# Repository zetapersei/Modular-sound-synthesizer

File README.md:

# Analog Modular Synthesizer

An analog modular synthesizer project inspired by the architecture of classic
synthesizers, including those in the Moog tradition. It grew out of a personal
project I worked on between 1978 and 1980; the schematics preserve that idea
and have since been collected and redrawn in KiCad.

The repository contains the project's electronic design documentation: a
hierarchical top-level schematic, individual module schematics, a PCB project,
and a netlist.

## Modules

| Module | Function |
| --- | --- |
| **VCO** | Voltage-controlled oscillator: generates the basic signal. |
| **VCF** | Voltage-controlled filter, identified in the schematic as the PAiA 4730 filter. |
| **VCA** | Voltage-controlled amplifier: controls the signal level. |
| **ADSR** | Envelope generator for shaping the sound over time. |
| **LFO** | Low-frequency oscillator for slow modulation. |
| **Noise generator** | Noise source for additional timbres and modulation. |
| **Audio mixer** | Combines audio sources. |
| **Keyboard encoder** | Schematic for a 49-key musical keyboard interface. |

The modules are organized in the main schematic
[`analog_synth.kicad_sch`](analog_synth.kicad_sch); each circuit also has its
own separate schematic. Module filenames correspond to the names in the table.

## Opening the project

Open [`analog_synth.kicad_pro`](analog_synth.kicad_pro) in KiCad to access the
project, hierarchical schematic, and PCB
[`analog_synth.kicad_pcb`](analog_synth.kicad_pcb). You can also open the main
schematic file directly.

## Project status

The schematics document the architecture and circuits, but the repository
does not specify whether the hardware has been built or tested. Before building
or powering the circuits, verify the schematics, netlist, footprints,
components, and required voltages.

## License

The project is distributed under the GNU GPL version 3; see [`LICENSE`](LICENSE)
for the full text.

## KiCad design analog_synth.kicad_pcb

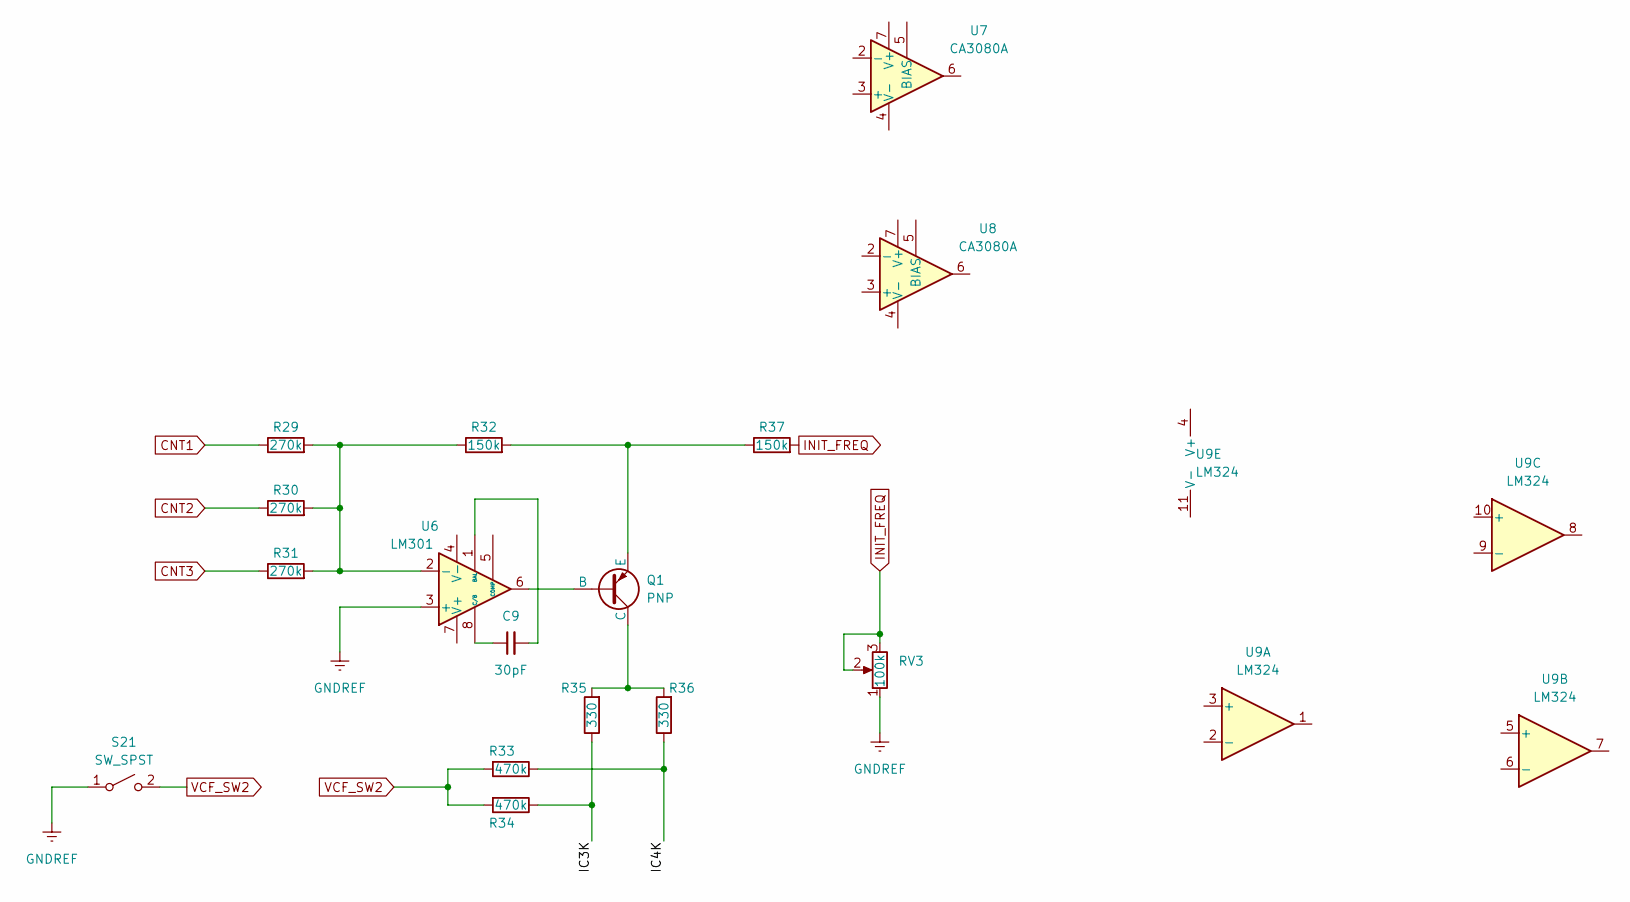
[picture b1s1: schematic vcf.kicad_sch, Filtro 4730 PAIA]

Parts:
C9: 30pF; C_1210_3225Metric
Q1: PNP
R29, R30, R31: 270k; R_1206_3216Metric
R32, R37: 150k; R_1206_3216Metric
R33, R34: 470k; R_1206_3216Metric
R35, R36: 330; R_1206_3216Metric
RV3: 100k; R_1206_3216Metric
S21: SW_SPST
U6: LM301; DIP-8_W7.62mm_Socket
U7, U8: CA3080A; DIP-8_W7.62mm_Socket
U9: LM324; DIP-14_W7.62mm_Socket

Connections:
/VCF/IC3K: R34.1, R35.1
/VCF/IC4K: R33.1, R36.1
CNT1: R29.1
CNT2: R30.1
CNT3: R31.1
GNDREF: RV3.1, S21.1 (A), U6.3 (+); also elsewhere on the board
INIT_FREQ: R37.2, RV3.2, RV3.3
unnamed: Q1.2 (B), U6.6
unnamed: Q1.1 (C), R35.2, R36.2
unnamed: Q1.3 (E), R32.2, R37.1
unnamed: R29.2, R30.2, R31.2, R32.1, U6.2 (-)
unnamed: C9.2, U6.1 (BAL)
unnamed: C9.1, U6.8 (C/B)
VCF_SW2: R33.2, R34.2, S21.2 (B)

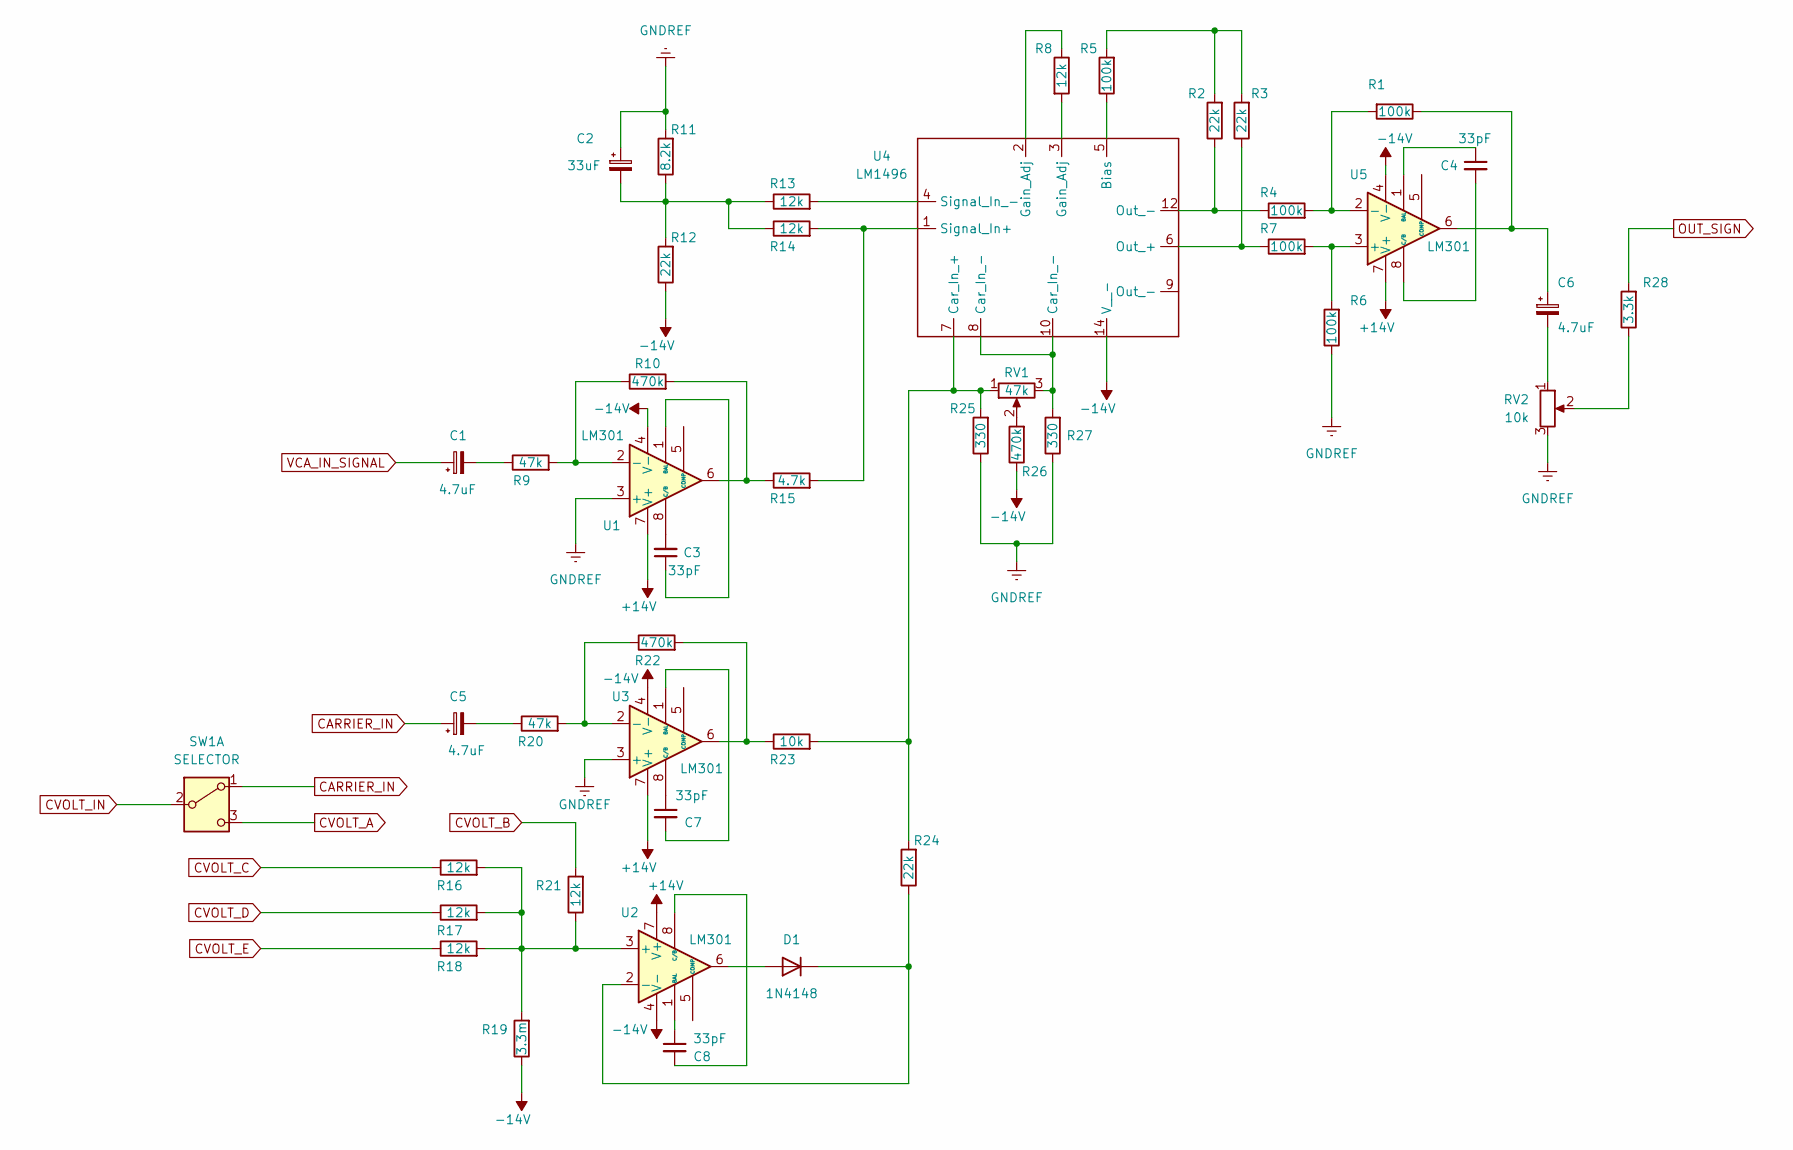
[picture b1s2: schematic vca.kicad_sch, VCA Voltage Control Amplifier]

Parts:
C1, C5, C6: 4.7uF; C_1210_3225Metric
C2: 33uF; C_1210_3225Metric
C3, C4, C7, C8: 33pF; C_1210_3225Metric
D1: 1N4148; D_DO-35_SOD27_P7.62mm_Horizontal
R1, R4, R5, R6, R7: 100k; R_1206_3216Metric
R2, R3, R12, R24: 22k; R_1206_3216Metric
R8, R13, R14, R16, R17, R18, R21: 12k; R_1206_3216Metric
R9, R20: 47k; R_1206_3216Metric
R10, R22, R26: 470k; R_1206_3216Metric
R11: 8.2k; R_1206_3216Metric
R15: 4.7k; R_1206_3216Metric
R19: 3.3m; R_1206_3216Metric
R23: 10k; R_1206_3216Metric
R25, R27: 330; R_1206_3216Metric
R28: 3.3k; R_1206_3216Metric
RV1: 47k; R_1206_3216Metric
RV2: 10k; R_1206_3216Metric
SW1: SELECTOR
U1, U2, U3, U5: LM301; DIP-8_W7.62mm_Socket
U4: LM1496; DIP-14_W7.62mm_Socket

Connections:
+14V: U1.7 (V+), U2.7 (V+), U3.7 (V+), U5.7 (V+)
-14V: R12.1, R19.1, R26.1, U1.4 (V-), U2.4 (V-), U3.4 (V-), U4.14 (V__-), U5.4 (V-)
CARRIER_IN: C5.1, SW1.1 (A)
CVOLT_B: R21.2
CVOLT_C: R16.1
CVOLT_D: R17.1
CVOLT_E: R18.1
GNDREF: C2.1, R6.1, R11.2, R25.1, R27.1, RV2.3, U1.3 (+), U3.3 (+); also elsewhere on the board
unnamed: C1.2, R9.1
unnamed: C2.2, R11.1, R12.2, R13.1, R14.1
unnamed: C5.2, R20.1
unnamed: C6.1, R1.1, U5.6
unnamed: C6.2, RV2.1
unnamed: D1.2 (A), U2.6
unnamed: D1.1 (K), R24.1, U2.2 (-)
unnamed: R2.1, R4.1, U4.12 (Out_-)
unnamed: R2.2, R3.2, R5.2
unnamed: R8.1, U4.2 (Gain_Adj)
unnamed: R8.2, U4.3 (Gain_Adj)
unnamed: R10.2, R15.1, U1.6
unnamed: R22.2, R23.1, U3.6
unnamed: R26.2, RV1.2
unnamed: R27.2, RV1.3, U4.8 (Car_In_-), U4.10 (Car_In_-)
unnamed: R28.1, RV2.2
unnamed: R9.2, R10.1, U1.2 (-)
unnamed: C3.1, U1.1 (BAL)
unnamed: C3.2, U1.8 (C/B)
unnamed: R16.2, R17.2, R18.2, R19.2, R21.1, U2.3 (+)
unnamed: C8.1, U2.1 (BAL)
unnamed: C8.2, U2.8 (C/B)
unnamed: R20.2, R22.1, U3.2 (-)
unnamed: C7.2, U3.1 (BAL)
unnamed: C7.1, U3.8 (C/B)
unnamed: R5.1, U4.5 (Bias)
unnamed: R23.2, R24.2, R25.2, RV1.1, U4.7 (Car_In_+)
unnamed: R3.1, R7.1, U4.6 (Out_+)
unnamed: R14.2, R15.2, U4.1 (Signal_In+)
unnamed: R13.2, U4.4 (Signal_In_-)
unnamed: R6.2, R7.2, U5.3 (+)
unnamed: R1.2, R4.2, U5.2 (-)
unnamed: C4.1, U5.1 (BAL)
unnamed: C4.2, U5.8 (C/B)
OUT_SIGN: R28.2
VCA_IN_SIGNAL: C1.1

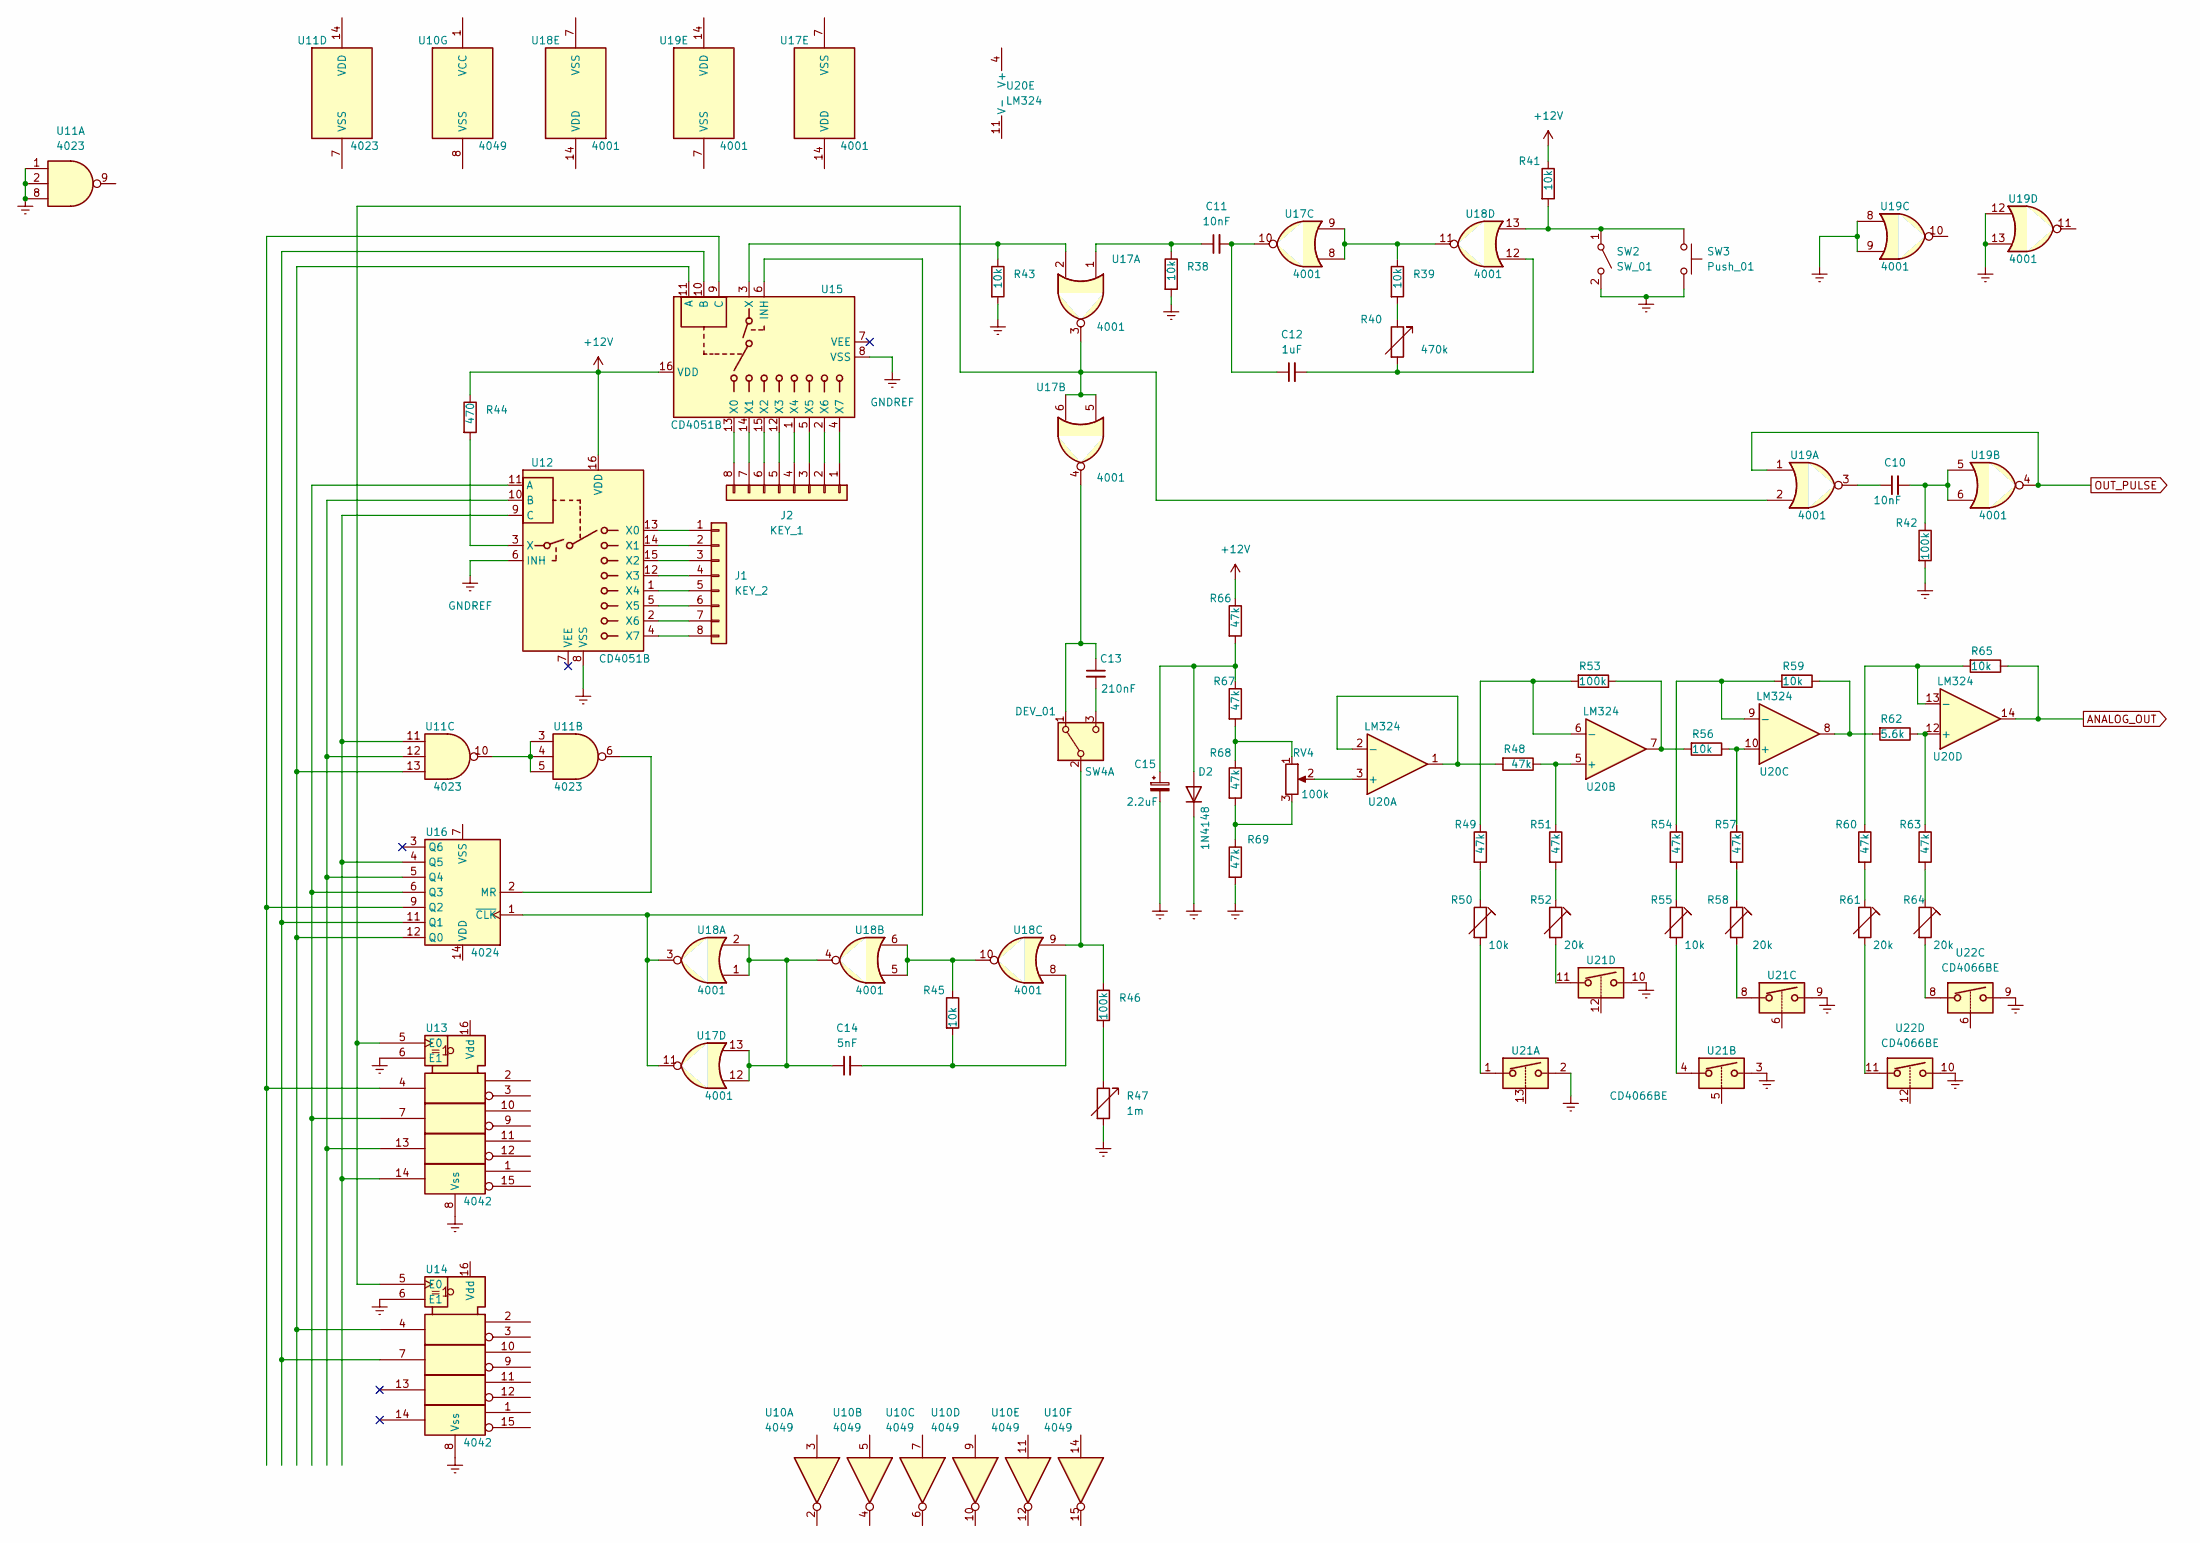
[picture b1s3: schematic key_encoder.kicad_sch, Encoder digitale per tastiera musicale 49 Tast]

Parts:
C10, C11: 10nF; C_1210_3225Metric
C12: 1uF; C_1210_3225Metric
C13: 210nF; C_1210_3225Metric
C14: 5nF; C_1210_3225Metric
C15: 2.2uF; C_1210_3225Metric
D2: 1N4148; D_DO-35_SOD27_P7.62mm_Horizontal
J1: KEY_2
J2: KEY_1
R38, R39, R41, R43, R45, R56, R59, R65: 10k; R_1206_3216Metric
R40: 470k; R_1206_3216Metric
R42, R46, R53: 100k; R_1206_3216Metric
R44: 470; R_1206_3216Metric
R47: 1m; R_1206_3216Metric
R48, R49, R51, R54, R57, R60, R63, R66, R67, R68, R69: 47k; R_1206_3216Metric
R50, R55: 10k; Potentiometer_Bourns_3009P_Horizontal
R52, R58, R61, R64: 20k; Potentiometer_Bourns_3009P_Horizontal
R62: 5.6k; R_1206_3216Metric
RV4: 100k; R_1206_3216Metric
SW2: SW_01
SW3: Push_01
SW4: DEV_01
U10: 4049; DIP-14_W7.62mm_Socket
U11: 4023; DIP-14_W7.62mm_Socket
U12, U15: CD4051B; DIP-16_W7.62mm_Socket
U13, U14: 4042; DIP-14_W7.62mm_Socket
U16: 4024; DIP-14_W7.62mm_Socket
U17, U18, U19: 4001; DIP-14_W7.62mm_Socket
U20: LM324; DIP-14_W7.62mm_Socket
U21, U22: CD4066BE; DIP-14_W7.62mm_Socket

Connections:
+12V: R41.1, R44.1, R66.1, U12.16 (VDD), U15.16 (VDD)
ANALOG_OUT: R65.1, U20.14
GNDREF: C15.2, D2.1 (K), R38.2, R42.2, R43.2, R47.2, R69.2, SW2.2 (B), SW3.2, U11.1, U11.2, U11.8, U12.6 (INH), U12.8 (VSS), U13.6 (E1), U13.8 (Vss), U14.6 (E1), U14.8 (Vss), U15.8 (VSS), U19.8, U19.9, U19.12, U19.13, U21.2, U21.3, U21.9, U21.10, U22.9, U22.10; also elsewhere on the board
unnamed: C10.1, U19.3
unnamed: C10.2, R42.1, U19.5, U19.6
unnamed: C11.1, R38.1, U17.1
unnamed: C11.2, C12.1, U17.10
unnamed: C12.2, R40.2, U18.12
unnamed: C14.1, U17.12, U17.13, U18.1, U18.2, U18.4
unnamed: C14.2, R45.2, U18.8
unnamed: C15.1, D2.2 (A), R66.2, R67.1
unnamed: J1.1, U12.13 (X0)
unnamed: J1.2, U12.14 (X1)
unnamed: J1.3, U12.15 (X2)
unnamed: J1.4, U12.12 (X3)
unnamed: J1.5, U12.1 (X4)
unnamed: J1.6, U12.5 (X5)
unnamed: J1.7, U12.2 (X6)
unnamed: J1.8, U12.4 (X7)
unnamed: J2.1, U15.4 (X7)
unnamed: J2.2, U15.2 (X6)
unnamed: J2.3, U15.5 (X5)
unnamed: J2.4, U15.1 (X4)
unnamed: J2.5, U15.12 (X3)
unnamed: J2.6, U15.15 (X2)
unnamed: J2.7, U15.14 (X1)
unnamed: J2.8, U15.13 (X0)
unnamed: R39.1, U17.8, U17.9, U18.11
unnamed: R39.2, R40.1
unnamed: R45.1, U18.5, U18.6, U18.10
unnamed: R46.2, R47.1
unnamed: R49.2, R50.1
unnamed: R50.2, U21.1
unnamed: R51.2, R52.1
unnamed: R52.2, U21.11
unnamed: R53.1, R56.2, U20.7
unnamed: R54.2, R55.1
unnamed: R55.2, U21.4
unnamed: R57.2, R58.1
unnamed: R58.2, U21.8
unnamed: R59.1, R62.2, U20.8
unnamed: R60.2, R61.1
unnamed: R61.2, U22.11
unnamed: R63.2, R64.1
unnamed: R64.2, U22.8
unnamed: R67.2, R68.1, RV4.1
unnamed: R68.2, R69.1, RV4.3
unnamed: R41.2, SW2.1 (A), SW3.1, U18.13
unnamed: C13.1, SW4.1 (A), U17.4
unnamed: R46.1, SW4.2 (B), U18.9
unnamed: C13.2, SW4.3 (C)
unnamed: U11.3, U11.4, U11.5, U11.10
unnamed: U12.11 (A), U13.7, U16.6 (Q3)
unnamed: U11.12, U12.10 (B), U13.13, U16.5 (Q4)
unnamed: U11.11, U12.9 (C), U13.14, U16.4 (Q5)
unnamed: R44.2, U12.3 (X)
unnamed: U13.5 (E0), U14.5 (E0), U17.3, U17.5, U17.6, U19.2
unnamed: U11.13, U14.4, U15.11 (A), U16.12 (Q0)
unnamed: U14.7, U15.10 (B), U16.11 (Q1)
unnamed: U13.4, U15.9 (C), U16.9 (Q2)
unnamed: U15.6 (INH), U16.1 (~CLK), U17.11, U18.3
unnamed: R43.1, U15.3 (X), U17.2
unnamed: U11.6, U16.2 (MR)
unnamed: RV4.2, U20.3 (+)
unnamed: R48.2, U20.1, U20.2 (-)
unnamed: R48.1, R51.1, U20.5 (+)
unnamed: R49.1, R53.2, U20.6 (-)
unnamed: R56.1, R57.1, U20.10 (+)
unnamed: R54.1, R59.2, U20.9 (-)
unnamed: R62.1, R63.1, U20.12 (+)
unnamed: R60.1, R65.2, U20.13 (-)
OUT_PULSE: U19.1, U19.4

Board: 2 copper layers, 112 parts (0 on the bottom side), 100 nets, no tracks yet.

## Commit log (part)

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2025-07-17 Create LICENSE
2025-07-17 nuovo file: adsr.kicad_pcb nuovo file: adsr.kicad_pro nuovo file: adsr.kicad_sch nuovo file: analog_synth.kicad_pcb nuovo file: analog_synth.kicad_prl nuovo file: analog_synth.kicad_pro nuovo file: a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
2025-07-18 modificato: analog_synth.kicad_pro modificato: fp-info-cache nuovo file: operational.bak nuovo file: operational.kicad_sym nuovo file: sym-lib-table nuovo file: vca.kicad_prl modificato: vca.kicad_sc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
2025-07-18 modificato: operational.bak modificato: operational.kicad_sym modificato: vca.kicad_sch
2025-07-19 modificato: analog_synth.kicad_pro modificato: key_encoder.kicad_sch modificato: vca.kicad_pro modificato: vca.kicad_sch nuovo file: vca.net modificato: vcf.kicad_sch
2025-07-20 modificato: key_encoder.kicad_sch
2025-07-30 eliminato: adsr.kicad_pcb eliminato: adsr.kicad_pro modificato: analog_synth.kicad_pcb nuovo file: analog_synth.net eliminato: audio_mixer.kicad_pcb eliminato: audio_mixer.kicad_pro eliminato: key_en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
2025-07-30 modificato: analog_synth.kicad_pcb modificato: key_encoder.kicad_sch
2026-04-04 Add simple calculator implementation
